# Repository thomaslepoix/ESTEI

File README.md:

# [Fr] ESTEI - Travaux réalisés dans le cadre de l'école

<br>

## M2 - Projet : Autoscope
### Description
- Création d'un télescope robotisé imprimable en 3D basé sur une Raspberry Pi et le logiciel [Stellarium](http://stellarium.org/).
- Création d'une carte d'extension de la Raspberry Pi.
- Création de l'OS de la Raspberry Pi avec [Yocto](https://www.yoctoproject.org/).
- Création d'un daemon pour le GPS mtk3339 ([Adafruit ultimate GPS](https://www.adafruit.com/product/746))
- Travail en collaboration avec [Thibaud Le Doledec](https://github.com/thibaudledo), [Thomas Abgrall](https://github.com/ThomasAbg) et [Clément Ailloud](https://github.com/clement-ailloud)
### Contenu
- [Rapport de projet](https://github.com/thibaudledo/Autoscope/blob/latex/Autoscope_6.pdf)
- [Dépôt principal du projet](https://github.com/thibaudledo/Autoscope)
- [Fichiers de production de la carte d'extension (KiCad)](https://github.com/thibaudledo/Autoscope/tree/hardware)
- [Daemon mtk3339d](https://github.com/thibaudledo/Autoscope/tree/mtk3339d)
- [Layer Yocto de l'OS](https://github.com/thomaslepoix/meta-autoscope)

<br>
<br>

## M2 - ARM : TPs STM32F4
### Description
- TP1 : Utilisation du bouton pour contrôler les LEDs, en polling et avec interruptions.
- TP2 : Utilisation d'une PWM pour contrôler l'intensité lumineuse des LEDs.
### Contenu
- [Rapport TP1](https://github.com/thomaslepoix/ESTEI/blob/master/M2_ARM_TPs_STM32F4/TP1_IO_Interruptions/TP1.pdf)
- [Sources TP1](https://github.com/thomaslepoix/ESTEI/blob/master/M2_ARM_TPs_STM32F4/TP1_IO_Interruptions/Sources)
- [Rapport TP2](https://github.com/thomaslepoix/ESTEI/blob/master/M2_ARM_TPs_STM32F4/TP2_PWM/TP2.pdf)
- [Sources TP2](https://github.com/thomaslepoix/ESTEI/blob/master/M2_ARM_TPs_STM32F4/TP2_PWM/Sources)

<br>
<br>

## M2 - C++ : Qucs-RFlayout
### Description
- Développement d'une solution pour produire des typons à partir des schémas microstrips de [Qucs](http://qucs.sourceforge.net/).
- Via [PcbNew](http://kicad-pcb.org/discover/pcbnew/) ou [pcb-rnd](http://repo.hu/projects/pcb-rnd/).
### Contenu
- [Rapport de projet](https://github.com/thomaslepoix/ESTEI/blob/master/M2_CPP_Qucs-RFlayout/Qucs-RFlayout.pdf)
- [Dépôt du projet](https://github.com/thomaslepoix/Qucs-RFlayout)

<br>
<br>

## M1 - Projet : Télécommande Wifi basée sur une Raspberry Pi
### Description
- Création d'une carte d'IHM pluggable sur la Raspberry Pi.
- Création de l'OS de la Raspberry Pi avec [Yocto](https://www.yoctoproject.org/).
- Travail en collaboration avec [Thibaud LE DOLEDEC](https://www.hackster.io/thibaud-le-doledec/) et [Taha MENEBHI](https://www.linkedin.com/in/taha-menebhi/).
### Contenu
- [Rapport de projet](https://github.com/thomaslepoix/ESTEI/blob/master/M1_Projet_Telecommande_Raspberry-Pi/Hardware_Middleware.pdf)
- [Rapport complet avec Thibaud LE DOLEDEC et Taha MENEBHI](https://github.com/thomaslepoix/ESTEI/blob/master/M1_Projet_Telecommande_Raspberry-Pi/Projet.pdf)
- [Diaporama de présentation](https://github.com/thomaslepoix/ESTEI/blob/master/M1_Projet_Telecommande_Raspberry-Pi/Oral.pdf)
- [Layer Yocto de l'OS](https://github.com/thomaslepoix/meta-remote-estei)
- [Fichiers de production de la carte d'IHM (KiCad)](https://github.com/thomaslepoix/ESTEI/tree/master/M1_Projet_Telecommande_Raspberry-Pi/PCB_kicad)

<br>
<br>

## M1 - Hyperfréquences : TP3 Antennes patch
### Description
- Simulation et production d'antennes patch avec [Qucs](http://qucs.sourceforge.net/), [OpenEMS](http://openems.de/start/index.php) et [GNU Octave](https://www.gnu.org/software/octave/).
### Contenu
- [Rapport de TP](https://github.com/thomaslepoix/ESTEI/blob/master/M1_Hyperfrequences_Antennes/TP3.pdf)
- [Manuel d'utilisation d'OpenEMS](https://github.com/thomaslepoix/ESTEI/blob/master/M1_Hyperfrequences_Antennes/OpenEMS.pdf)
- [Fichiers de travail (Qucs)](https://github.com/thomaslepoix/ESTEI/blob/master/M1_Hyperfrequences_Antennes/TP3_qucs_prj)
- [Fichiers de travail (GNU Octave / OpenEMS)](https://github.com/thomaslepoix/ESTEI/blob/master/M1_Hyperfrequences_Antennes/TP3_octave)

<br>
<br>

## M1 - Hyperfréquences : TP2 Filtres microstrip
### Description
- Simulation et production de filtres microstrip avec [Qucs](http://qucs.sourceforge.net/).
- Prototypage d'une solution pour produire des typons à partir des schémas microstrips de Qucs (via [PcbNew](http://kicad-pcb.org/discover/pcbnew/)).
### Contenu
- [Rapport de TP](https://github.com/thomaslepoix/ESTEI/blob/master/M1_Hyperfrequences_Filtres/TP2.pdf)
- [Diaporama de présentation](https://github.com/thomaslepoix/ESTEI/blob/master/M1_Hyperfrequences_Filtres/Oral.pdf)
- [Fichiers de travail (Qucs)](https://github.com/thomaslepoix/ESTEI/tree/master/M1_Hyperfrequences_Filtres/TP2_qucs_prj)
- [Scripts d'interfaçage de Qucs et PcbNew (en cours de développement)](https://github.com/thomaslepoix/QucstoKicad)

<br>
<br>

## B3 - Linux : TP Crosstool chain
### Description
- Réalisation manuelle d'un compilateur croisé x86 ARM.
- Automatisation du processus dans un script à l'interface ergonomique.
### Contenu
- [Rapport de TP](https://github.com/thomaslepoix/ESTEI/blob/master/B3_Linux_Crosstool_Chain/Compte_Rendu.pdf)
- [Script de construction du compilateur croisé](https://github.com/thomaslepoix/ESTEI/blob/master/B3_Linux_Crosstool_Chain/cross-compil.sh)

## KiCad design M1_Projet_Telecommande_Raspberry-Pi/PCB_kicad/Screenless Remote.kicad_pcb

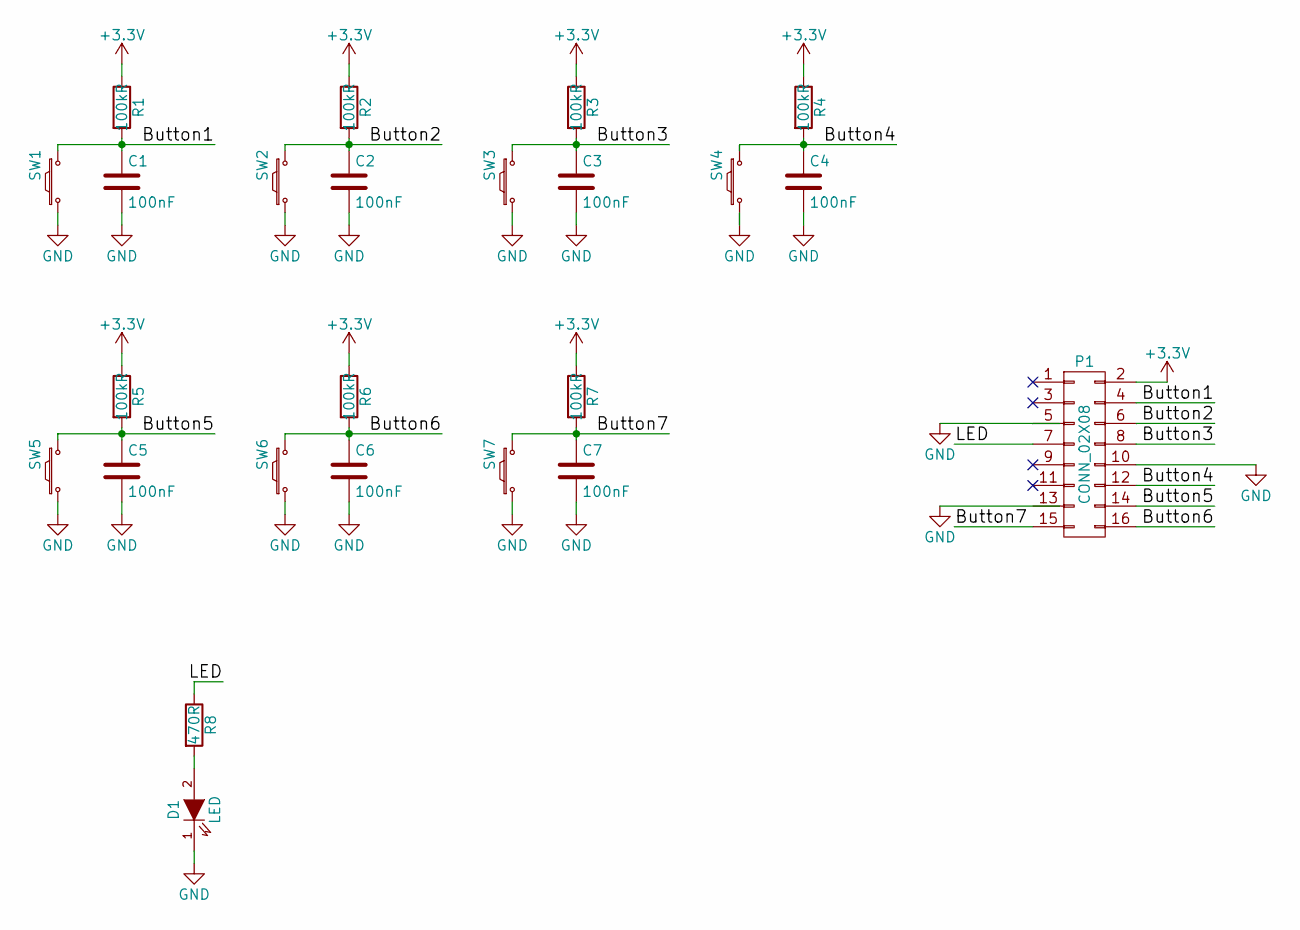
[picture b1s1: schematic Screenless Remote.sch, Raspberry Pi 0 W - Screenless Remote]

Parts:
C1, C2, C3, C4, C5, C6, C7: 100nF; C_0805_HandSoldering
D1: LED; C_1206_HandSoldering
P1: CONN_02X08; Pin_Header_Straight_2x08
R1, R2, R3, R4, R5, R6, R7: 100kR; R_0805_HandSoldering
R8: 470R; R_0805_HandSoldering
SW1, SW2, SW3, SW4, SW5, SW6, SW7: SW_PUSH_SMALL_H; KSC521G

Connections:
+3V3: P1.2, R1.1, R2.1, R3.1, R4.1, R5.1, R6.1, R7.1
/Button1: C1.1, P1.4, R1.2, SW1.2
/Button2: C2.1, P1.6, R2.2, SW2.2
/Button3: C3.1, P1.8, R3.2, SW3.2
/Button4: C4.1, P1.12, R4.2, SW4.2
/Button5: C5.1, P1.14, R5.2, SW5.2
/Button6: C6.1, P1.16, R6.2, SW6.2
/Button7: C7.1, P1.15, R7.2, SW7.2
/LED: P1.7, R8.1
GND: C1.2, C2.2, C3.2, C4.2, C5.2, C6.2, C7.2, D1.1 (K), P1.5, P1.10, P1.13, SW1.1, SW2.1, SW3.1, SW4.1, SW5.1, SW6.1, SW7.1
unnamed: D1.2 (A), R8.2

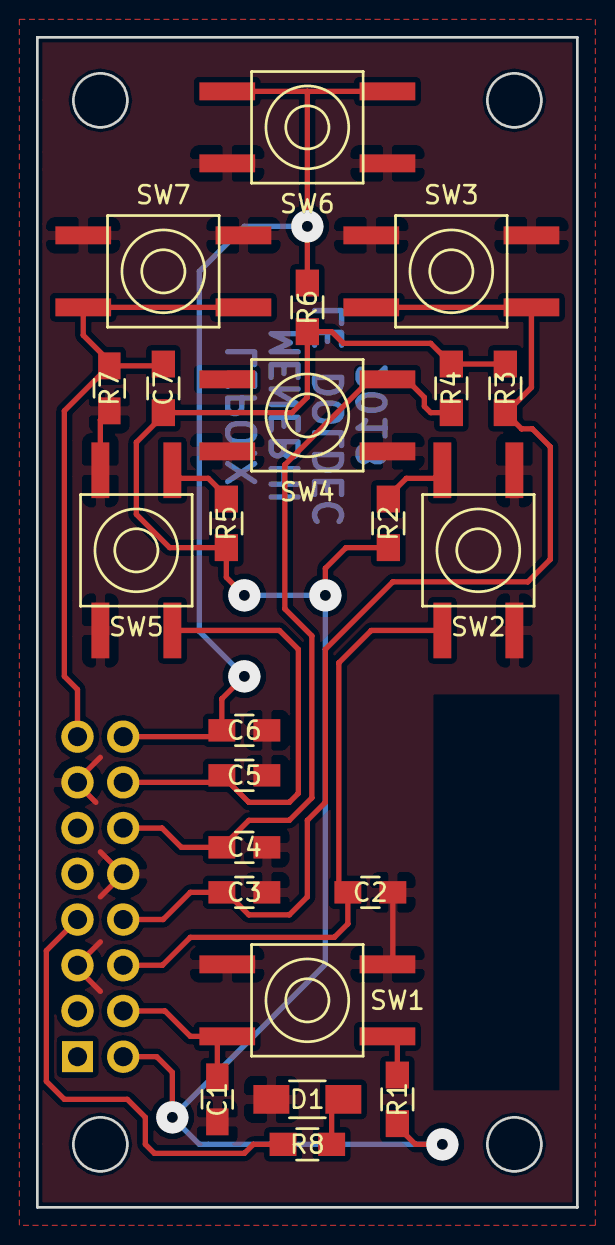
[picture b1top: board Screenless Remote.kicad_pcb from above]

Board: 2 copper layers, 30.0 x 65.0 mm, 24 parts (1 on the bottom side), 11 nets.

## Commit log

2017-03-14 Rename cross-compil.sh to B3_Linux_Crosstool_Chain/cross-compil.sh
2017-12-23 upload HF TP2
2018-04-11 add OpenEMS.pdf
2018-04-11 upload M1 project
2018-05-07 TP3 : add qucs and octave files
2018-05-07 add unfinished pdf
2018-05-07 update unfinished pdf
2018-05-11 update pdfs
2018-05-11 add figures
2018-05-14 add pcb, update pdfs
2018-11-20 link to thibaud hackster.io
2019-01-21 rm lost file
2019-01-21 add ARM TPs
2019-02-12 add Qucs-RFlayout to README
2019-05-22 make crosstool script executable
2019-05-22 add Qucs-RFlayout repport
2019-06-08 add autoscope to README
2019-06-14 add mtk3339d & hardware to autoscope
